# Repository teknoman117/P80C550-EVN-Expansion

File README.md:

P80C550-EVN Expansion Board Template
====================================

KiCad template for an expansion board for the P80C550-EVN

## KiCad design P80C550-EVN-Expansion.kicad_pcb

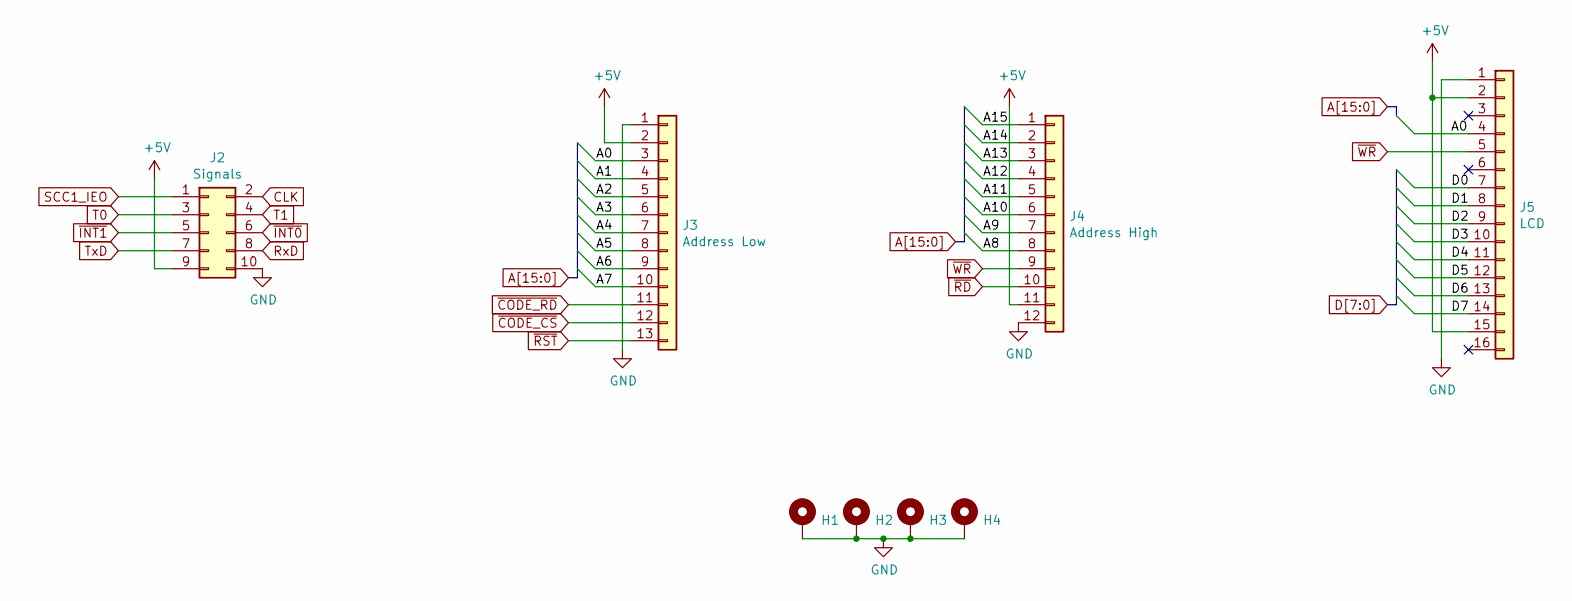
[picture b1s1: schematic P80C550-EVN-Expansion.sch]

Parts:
H1, H2, H3, H4: MountingHole_Pad; MountingHole_3.5mm_Pad_LCD
J2: Signals; PinSocket_2x05_P2.54mm_Vertical; Manufacturer_PN PPPC052LFBN-RC; Digikey_PN S7108-ND
J3: Address Low; PinSocket_1x13_P2.54mm_Vertical; Manufacturer_PN PPPC131LFBN-RC; Digikey_PN S7046-ND
J4: Address High; PinSocket_1x12_P2.54mm_Vertical; Manufacturer_PN PPPC131LFBN-RC; Digikey_PN S7046-ND
J5: LCD; PinSocket_1x16_P2.54mm_Vertical; Manufacturer_PN PPPC161LFBN-RC; Digikey_PN S7049-ND

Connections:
+5V: J2.9, J3.2, J4.11, J5.2, J5.15
/A0: J3.3, J5.4
/A1: J3.4
/A2: J3.5
/A3: J3.6
/A4: J3.7
/A5: J3.8
/A6: J3.9
/A7: J3.10
/A8: J4.8
/A9: J4.7
/A10: J4.6
/A11: J4.5
/A12: J4.4
/A13: J4.3
/A14: J4.2
/A15: J4.1
/D0: J5.7
/D1: J5.8
/D2: J5.9
/D3: J5.10
/D4: J5.11
/D5: J5.12
/D6: J5.13
/D7: J5.14
CLK: J2.2
GND: H1.1, H2.1, H3.1, H4.1, J2.10, J3.1, J4.12, J5.1
RxD: J2.8
SCC1_IEO: J2.1
T0: J2.3
T1: J2.4
TxD: J2.7
~CODE_CS: J3.12
~CODE_RD: J3.11
~INT0: J2.6
~INT1: J2.5
~RD: J4.10
~RST: J3.13
~WR: J4.9, J5.5

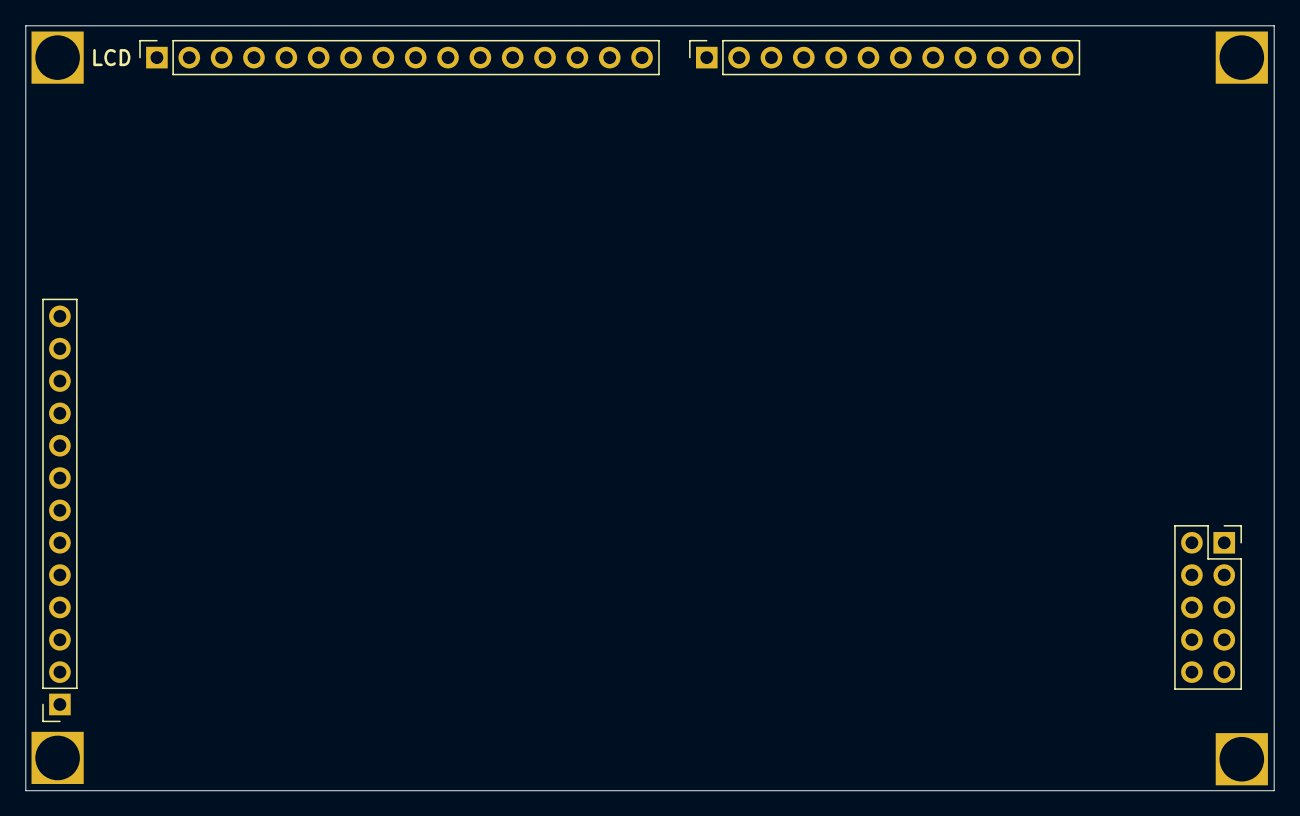
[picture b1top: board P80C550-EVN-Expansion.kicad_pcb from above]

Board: 4 copper layers, 98.0 x 60.1 mm, 8 parts (0 on the bottom side), 4 nets.

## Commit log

2021-07-24 template for expansion boards for the P80C550-EVN v1.0
